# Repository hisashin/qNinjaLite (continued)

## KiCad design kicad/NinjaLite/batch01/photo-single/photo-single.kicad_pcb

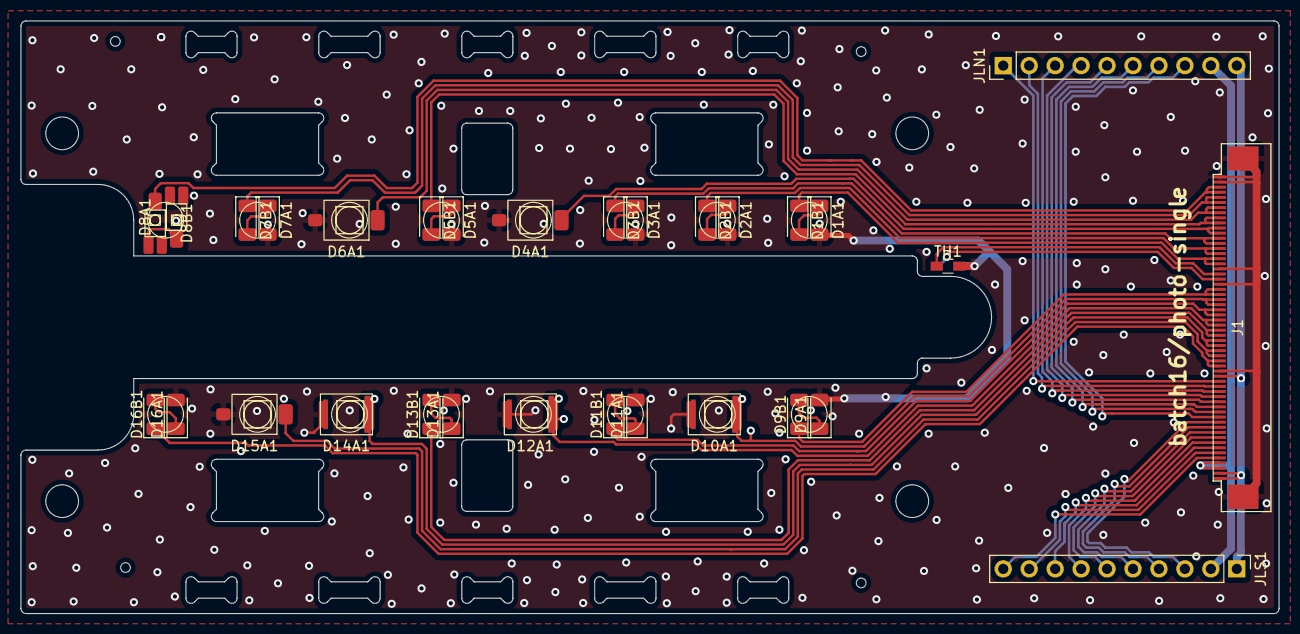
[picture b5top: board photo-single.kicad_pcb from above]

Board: 2 copper layers, 123.1 x 58.0 mm, 31 parts (1 on the bottom side), 47 nets.

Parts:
D1A1, D1B1, D2A1, D2B1, D3A1, D3B1, D5A1, D5B1, D7A1, D7B1, D9A1, D9B1, D11A1, D11B1, D13A1, D13B1, D16A1, D16B1: D_Photo; D_1206_3216Metric
D4A1, D6A1, D15A1: D_Photo; SFH2440_2430_BPW34S
D8A1, D8B1: D_Photo; SFH2400
D10A1, D12A1, D14A1: D_Photo; SFH2200_2201_2240
J1: Conn_01x60_Male; FFC_60_Ali_HUISHUNFA
JLN1: Conn_01x10_Male; Pin_Header_Straight_1x10_Pitch2.54mm
JLS1: Conn_01x10_Male; Pin_Header_Straight_1x10_Pitch2.54mm
TH1, TH2: Thermistor; R_0603_HandSoldering

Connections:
/N_LED_OUT9: J1.13, JLN1.8
/N_LED_OUT10: J1.14, JLN1.7
/N_LED_OUT11: J1.15, JLN1.6
/N_LED_OUT12: J1.16, JLN1.5
/N_LED_OUT13: J1.17, JLN1.4
/N_LED_OUT14: J1.18, JLN1.3
/N_LED_OUT15: J1.19, JLN1.2
/N_LED_OUT16: J1.20, JLN1.1
/N_PD_OUT1: D1B1.1 (K), J1.43, J1.44
/N_PD_OUT3: D2B1.1 (K), J1.45, J1.46
/N_PD_OUT5: D3B1.1 (K), J1.47, J1.48
/N_PD_OUT7: D4A1.1 (K), J1.49, J1.50
/N_PD_OUT9: D5B1.1 (K), J1.51, J1.52
/N_PD_OUT11: D6A1.1 (K), J1.53, J1.54
/N_PD_OUT13: D7B1.1 (K), J1.55, J1.56
/N_PD_OUT15: D8B1.1 (K), J1.57, J1.58
/S_LED_OUT1: J1.12, JLS1.3
/S_LED_OUT2: J1.11, JLS1.4
/S_LED_OUT3: J1.10, JLS1.5
/S_LED_OUT4: J1.9, JLS1.6
/S_LED_OUT5: J1.8, JLS1.7
/S_LED_OUT6: J1.7, JLS1.8
/S_LED_OUT7: J1.6, JLS1.9
/S_LED_OUT8: J1.5, JLS1.10
/S_PD_OUT1: D9B1.1 (K), J1.37, J1.38
/S_PD_OUT3: D10A1.1 (K), J1.35, J1.36
/S_PD_OUT5: D11B1.1 (K), J1.33, J1.34
/S_PD_OUT7: D12A1.1 (K), J1.31, J1.32
/S_PD_OUT9: D13B1.1 (K), J1.29, J1.30
/S_PD_OUT11: D14A1.1 (K), J1.27, J1.28
/S_PD_OUT13: D15A1.1 (K), J1.25, J1.26
/S_PD_OUT15: D16B1.1 (K), J1.23, J1.24
GNDA: D1A1.2 (A), D2A1.2 (A), D3A1.2 (A), D4A1.2 (A), D5A1.2 (A), D6A1.2 (A), D7A1.2 (A), D8A1.2 (A), D9A1.2 (A), D10A1.2 (A), D11A1.2 (A), D12A1.2 (A), D13A1.2 (A), D14A1.2 (A), D15A1.2 (A), D16A1.2 (A), J1.22, J1.39, J1.42, J1.59, J1.60, J1.G1, J1.G2, TH1.2, TH2.2
GNDL: J1.1, J1.2, J1.21, JLN1.10, JLS1.1
unnamed: D1A1.1 (K), D1B1.2 (A)
unnamed: D2A1.1 (K), D2B1.2 (A)
unnamed: D3A1.1 (K), D3B1.2 (A)
unnamed: D5A1.1 (K), D5B1.2 (A)
unnamed: D7A1.1 (K), D7B1.2 (A)
unnamed: D8A1.1 (K), D8B1.2 (A)
unnamed: D9A1.1 (K), D9B1.2 (A)
unnamed: D11A1.1 (K), D11B1.2 (A)
unnamed: D13A1.1 (K), D13B1.2 (A)
unnamed: D16A1.1 (K), D16B1.2 (A)
unnamed: J1.40, TH2.1
unnamed: J1.41, TH1.1
VCCL: J1.3, J1.4, JLN1.9, JLS1.2
